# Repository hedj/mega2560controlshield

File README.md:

# mega2560controlshield
Screw terminal board with pulldowns, zeners, MOSFET output buffers and 4 low-pass filters for PWM.

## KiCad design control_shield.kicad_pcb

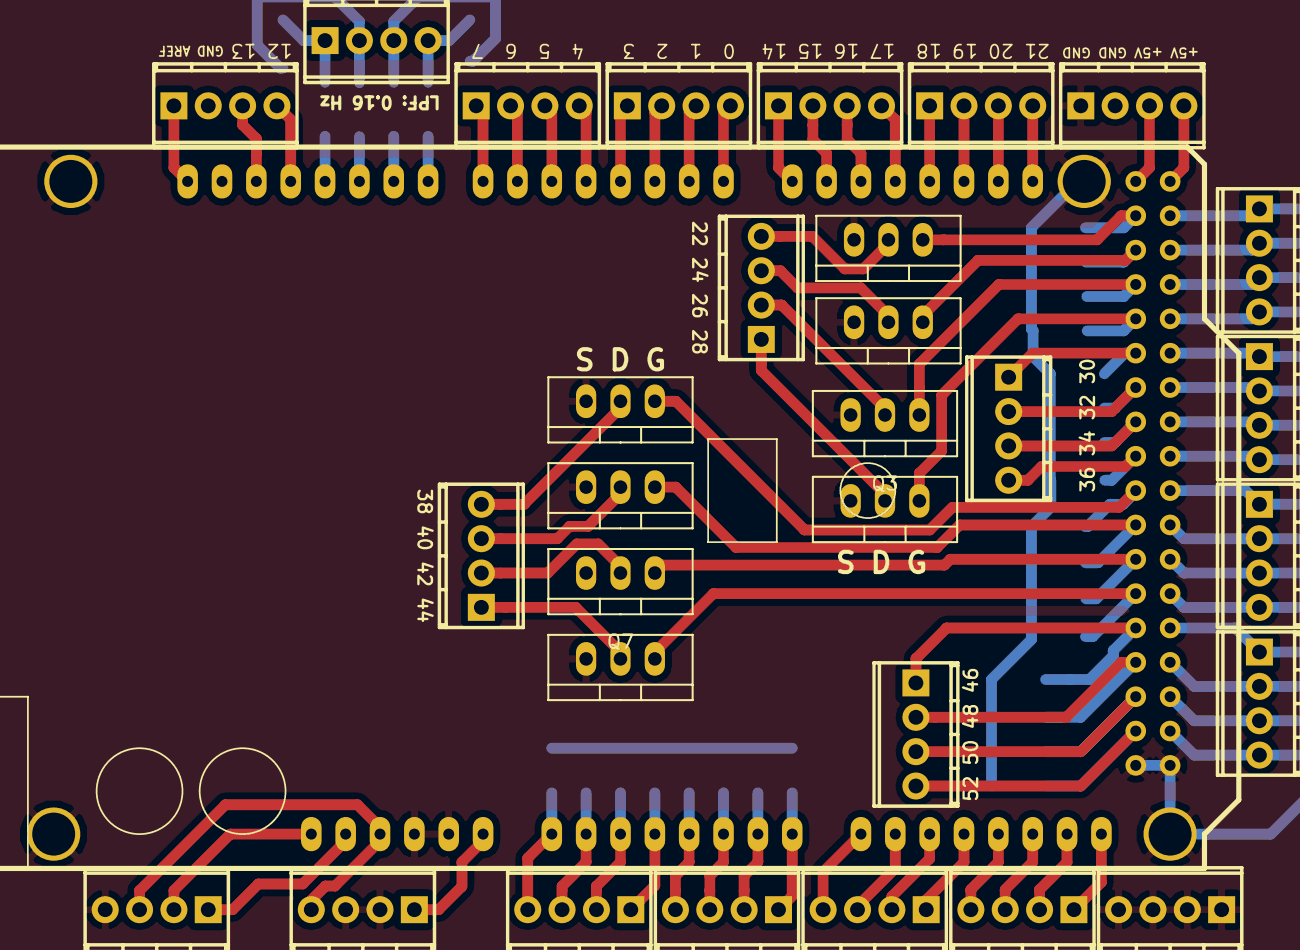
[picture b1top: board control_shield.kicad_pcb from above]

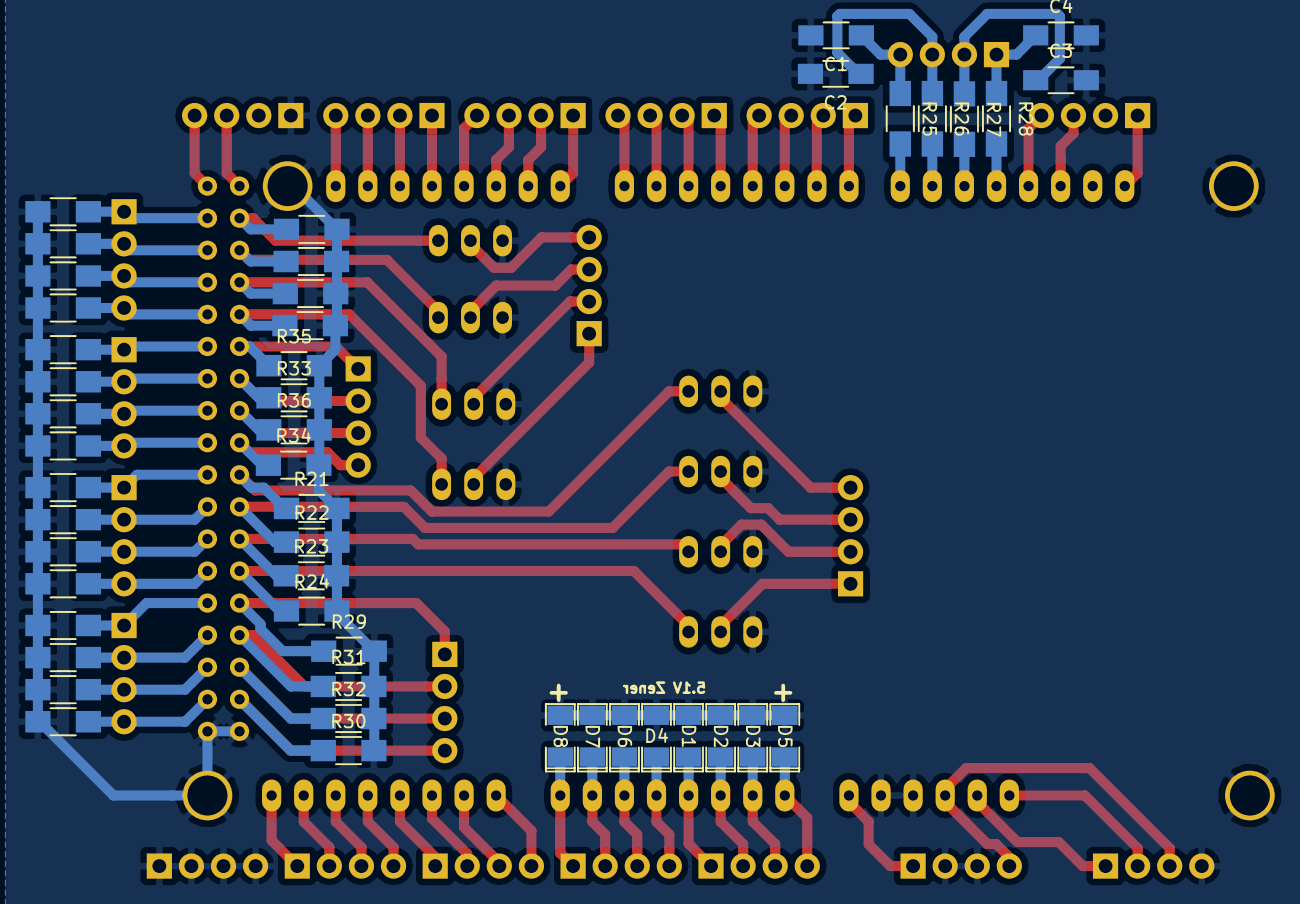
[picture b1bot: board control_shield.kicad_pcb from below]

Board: 2 copper layers, 79 parts (48 on the bottom side), 91 nets.

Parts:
C1, C2, C3, C4: 100u; C_1206_HandSoldering
D1, D2, D3, D4, D5, D6, D7, D8: ZENER; SMD-1206_Pol
P1, P2, P3, P4, P5, P6, P7, P8, P9, P10, P11, P12, P13, P14, P15, P16, P17, P18, P19, P20, P21, P22: CONN_01X04; mpt_0,5%2f4-2,54
Q1, Q2, Q3, Q4, Q5, Q6, Q7, Q8: Q_NMOS_GDS; TO-220_Neutral123_Vertical
R1, R2, R3, R4, R5, R6, R7, R8, R9, R10, R11, R12, R13, R14, R15, R16, R17, R18, R19, R20, R21, R22, R23, R24, R25, R26, R27, R28, R29, R30, R31, R32, R33, R34, R35, R36: 10k; R_1206_HandSoldering
SHIELD1: ARDUINO_MEGA_SHIELD

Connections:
GND: C1.2, C2.2, C3.2, C4.2, D1.2, D2.2, D3.2, D4.2, D5.2, D6.2, D7.2, D8.2, P19.1, P20.2, P20.3, P21.4, P22.1, P22.2, P22.3, P22.4, Q1.3, Q2.3, Q3.3, Q4.3, Q5.3, Q6.3, Q7.3, Q8.3, R1.2, R2.2, R3.2, R4.2, R5.2, R6.2, R7.2, R8.2, R9.2, R10.2, R11.2, R12.2, R13.2, R14.2, R15.2, R16.2, R17.2, R18.2, R19.2, R20.2, R21.2, R22.2, R23.2, R24.2, R29.2, R30.2, R31.2, R32.2, R33.2, R34.2, R35.2, R36.2, SHIELD1.GND1, SHIELD1.GND2, SHIELD1.GND4, SHIELD1.GND5
unnamed: C1.1, P6.4, R25.1
unnamed: C2.1, P6.3, R26.1
unnamed: C3.1, P6.2, R27.1
unnamed: C4.1, P6.1, R28.1
unnamed: D1.1, P11.1, SHIELD1.AD3
unnamed: D2.1, P11.2, SHIELD1.AD2
unnamed: D3.1, P11.3, SHIELD1.AD1
unnamed: D4.1, P13.4, SHIELD1.AD4
unnamed: D5.1, P11.4, SHIELD1.AD0
unnamed: D6.1, P13.3, SHIELD1.AD5
unnamed: D7.1, P13.2, SHIELD1.AD6
unnamed: D8.1, P13.1, SHIELD1.AD7
unnamed: P1.1, R8.1, SHIELD1.23
unnamed: P1.2, R7.1, SHIELD1.25
unnamed: P1.3, R6.1, SHIELD1.27
unnamed: P1.4, R5.1, SHIELD1.29
unnamed: P2.1, R4.1, SHIELD1.31
unnamed: P2.2, R3.1, SHIELD1.33
unnamed: P2.3, R2.1, SHIELD1.35
unnamed: P2.4, R1.1, SHIELD1.37
unnamed: P3.1, SHIELD1.AREF
unnamed: P3.2, SHIELD1.GND3
unnamed: P3.3, SHIELD1.13
unnamed: P3.4, SHIELD1.12
unnamed: P4.1, SHIELD1.7
unnamed: P4.2, SHIELD1.6
unnamed: P4.3, SHIELD1.5
unnamed: P4.4, SHIELD1.4
unnamed: P5.1, SHIELD1.14
unnamed: P5.2, SHIELD1.15
unnamed: P5.3, SHIELD1.16
unnamed: P5.4, SHIELD1.17
unnamed: P7.1, SHIELD1.3
unnamed: P7.2, SHIELD1.2
unnamed: P7.3, SHIELD1.1
unnamed: P7.4, SHIELD1.0
unnamed: P8.1, SHIELD1.18
unnamed: P8.2, SHIELD1.19
unnamed: P8.3, SHIELD1.20
unnamed: P8.4, SHIELD1.21
unnamed: P9.1, R9.1, SHIELD1.39
unnamed: P9.2, R10.1, SHIELD1.41
unnamed: P9.3, R11.1, SHIELD1.43
unnamed: P9.4, R12.1, SHIELD1.45
unnamed: P10.1, R16.1, SHIELD1.47
unnamed: P10.2, R15.1, SHIELD1.49
unnamed: P10.3, R14.1, SHIELD1.51
unnamed: P10.4, R13.1, SHIELD1.53
unnamed: P12.1, SHIELD1.AD11
unnamed: P12.2, SHIELD1.AD10
unnamed: P12.3, SHIELD1.AD9
unnamed: P12.4, SHIELD1.AD8
unnamed: P14.1, SHIELD1.AD15
unnamed: P14.2, SHIELD1.AD14
unnamed: P14.3, SHIELD1.AD13
unnamed: P14.4, SHIELD1.AD12
unnamed: P15.1, Q2.2
unnamed: P15.2, Q3.2
unnamed: P15.3, Q4.2
unnamed: P15.4, Q1.2
unnamed: P16.1, R35.1, SHIELD1.30
unnamed: P16.2, R33.1, SHIELD1.32
unnamed: P16.3, R36.1, SHIELD1.34
unnamed: P16.4, R34.1, SHIELD1.36
unnamed: P17.1, R29.1, SHIELD1.46
unnamed: P17.2, R31.1, SHIELD1.48
unnamed: P17.3, R32.1, SHIELD1.50
unnamed: P17.4, R30.1, SHIELD1.52
unnamed: P18.1, Q8.2
unnamed: P18.2, Q7.2
unnamed: P18.3, Q6.2
unnamed: P18.4, Q5.2
unnamed: P19.3, SHIELD1.5V_4
unnamed: P19.4, SHIELD1.5V_5
unnamed: P20.1, SHIELD1.V_IN
unnamed: P20.4, P21.3, SHIELD1.5V
unnamed: P21.1, SHIELD1.3V3
unnamed: P21.2, SHIELD1.RST
unnamed: Q1.1, R17.1, SHIELD1.22
unnamed: Q2.1, R18.1, SHIELD1.28
unnamed: Q3.1, R19.1, SHIELD1.26
unnamed: Q4.1, R20.1, SHIELD1.24
unnamed: Q5.1, R21.1, SHIELD1.38
unnamed: Q6.1, R22.1, SHIELD1.40
unnamed: Q7.1, R23.1, SHIELD1.42
unnamed: Q8.1, R24.1, SHIELD1.44
unnamed: R25.2, SHIELD1.8
unnamed: R26.2, SHIELD1.9
unnamed: R27.2, SHIELD1.10
unnamed: R28.2, SHIELD1.11
